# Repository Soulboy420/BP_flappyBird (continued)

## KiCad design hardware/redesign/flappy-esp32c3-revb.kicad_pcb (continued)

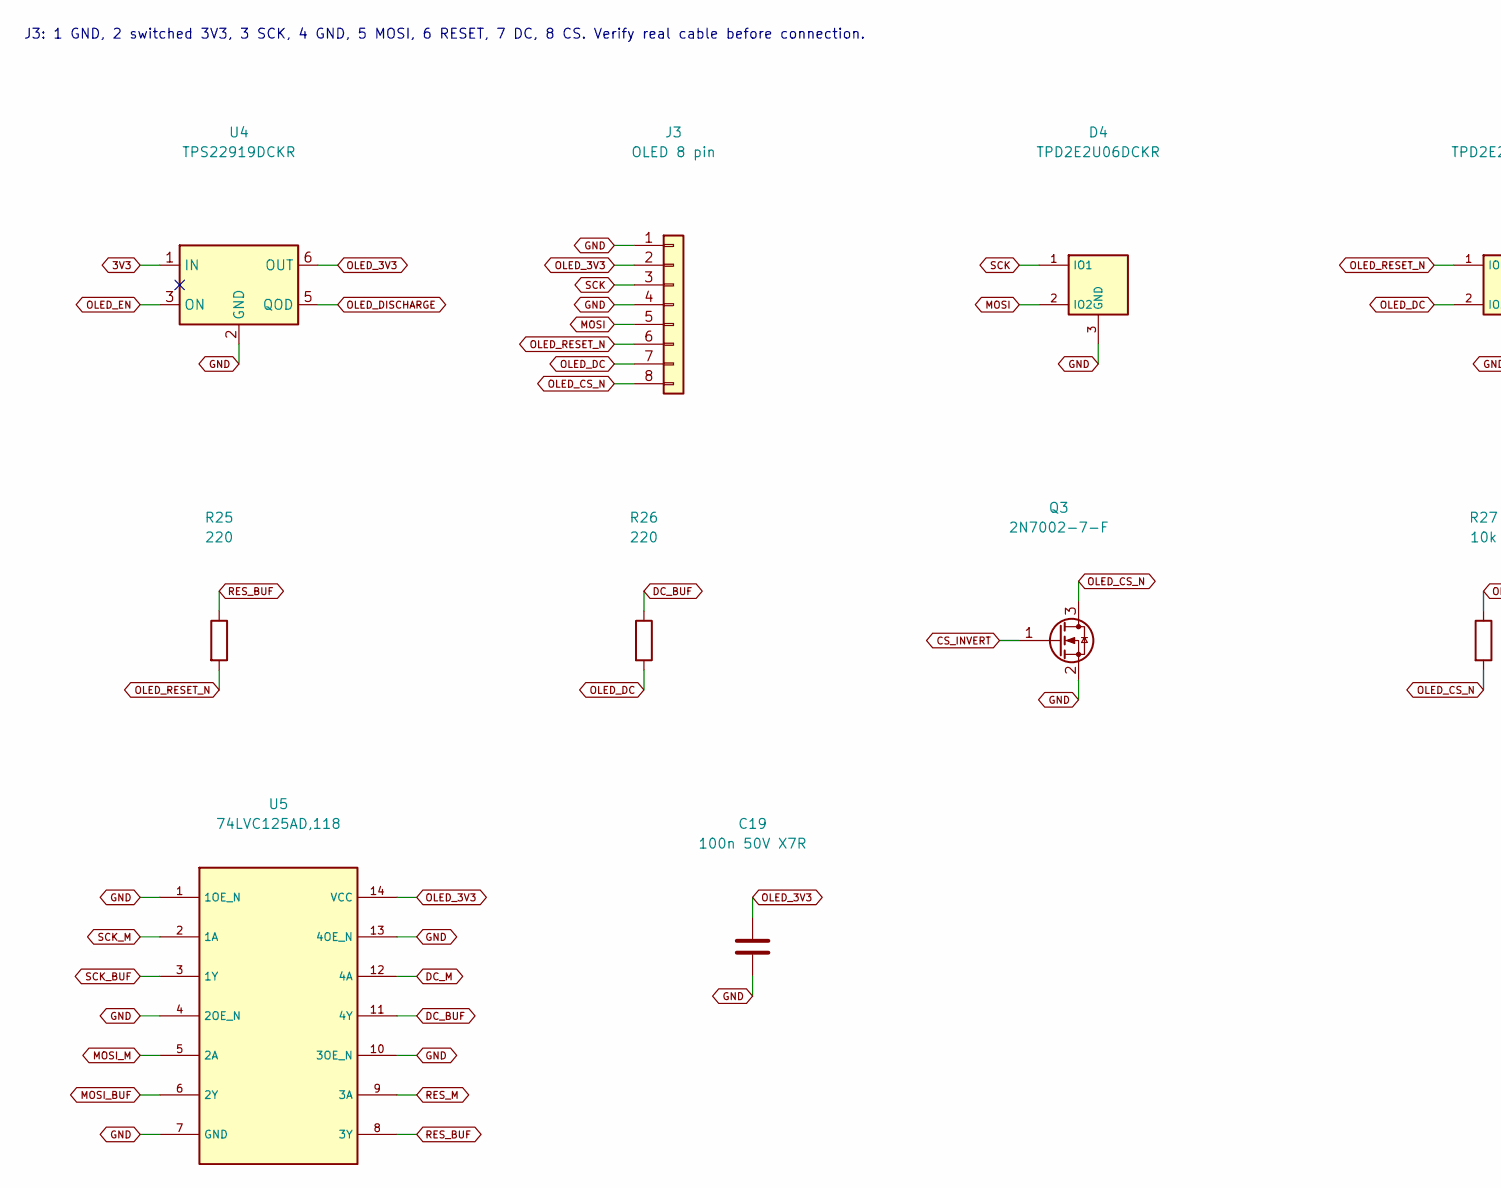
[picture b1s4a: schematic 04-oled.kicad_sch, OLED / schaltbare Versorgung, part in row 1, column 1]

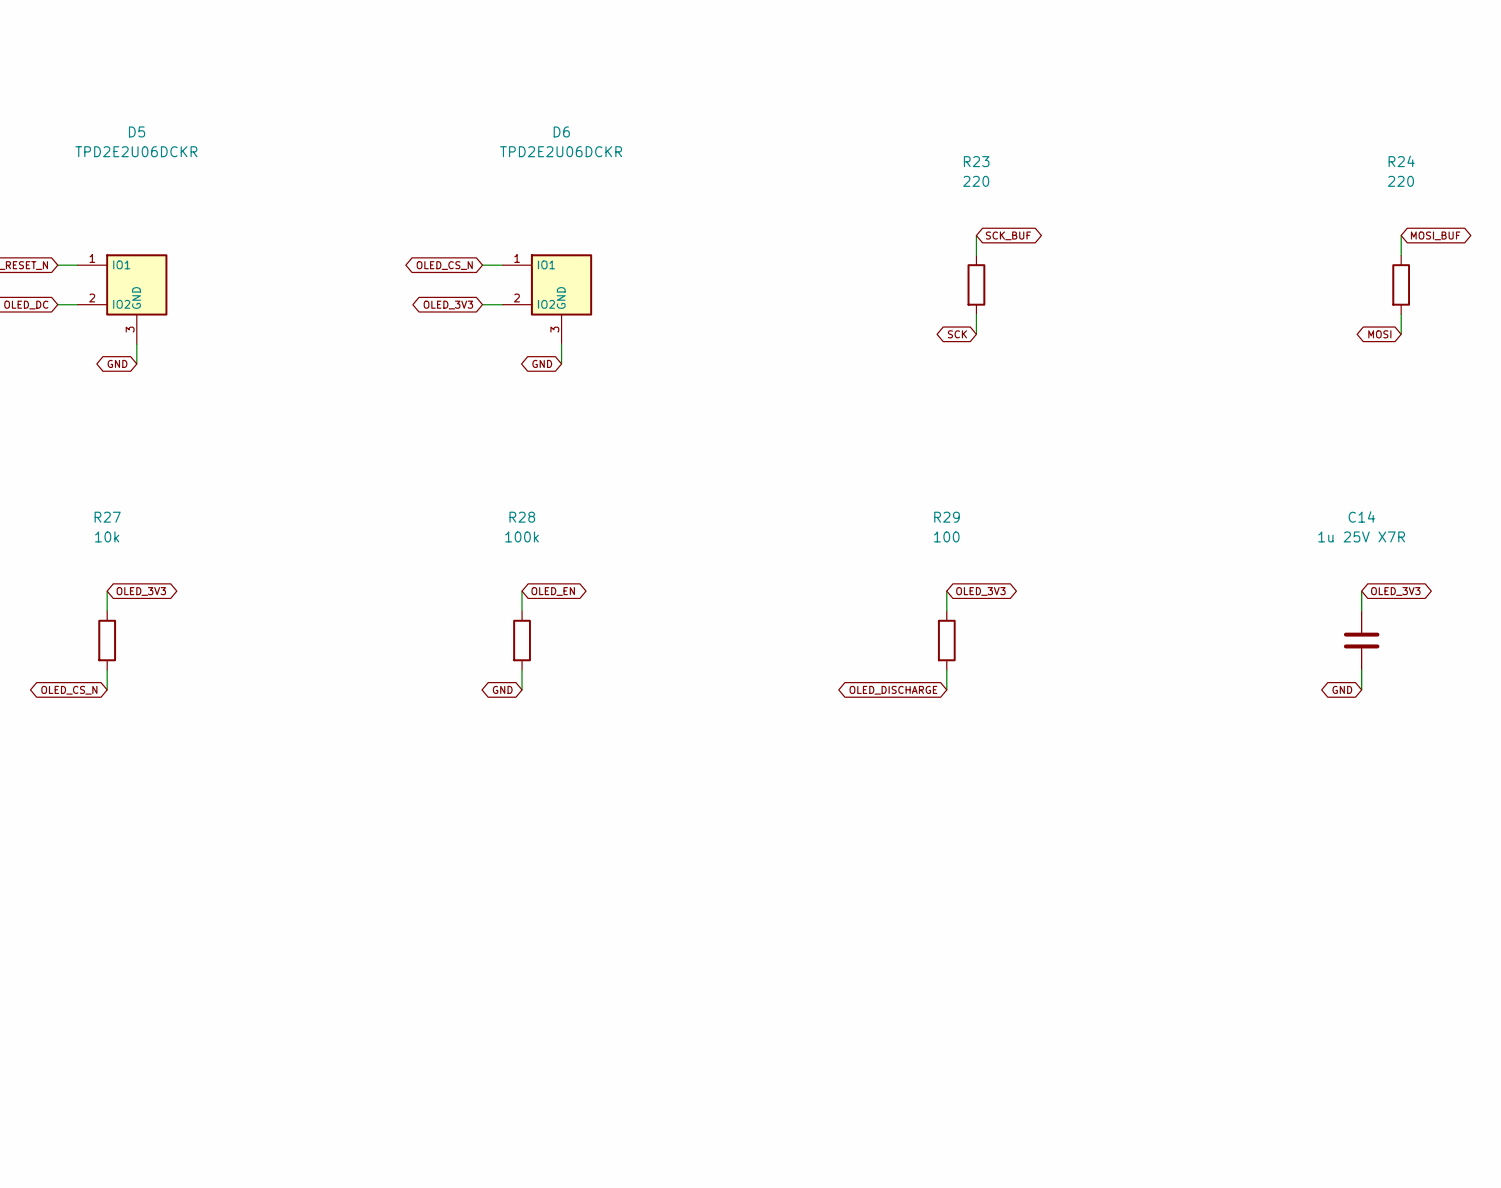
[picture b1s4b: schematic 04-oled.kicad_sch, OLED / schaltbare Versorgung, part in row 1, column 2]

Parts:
C14: 1u 25V X7R; Capacitor_SMD__C_0805_2012Metric_Pad1.18x1.45mm_HandSolder; MPN C2012X7R1E105K125AB
C19: 100n 50V X7R; Capacitor_SMD__C_0805_2012Metric_Pad1.18x1.45mm_HandSolder; MPN C2012X7R1H104K085AA
D4, D5, D6: TPD2E2U06DCKR; Package_TO_SOT_SMD__SOT-323_SC-70; MPN TPD2E2U06DCKR
J3: OLED 8 pin; Connector_JST__JST_XH_B8B-XH-A_1x08_P2.50mm_Vertical; MPN B8B-XH-A(LF)(SN)
Q3: 2N7002-7-F; Package_TO_SOT_SMD__SOT-23; MPN 2N7002-7-F
R23, R24, R25, R26: 220; Resistor_SMD__R_0805_2012Metric_Pad1.20x1.40mm_HandSolder; MPN ERJ-6ENF2200V
R27: 10k; Resistor_SMD__R_0805_2012Metric_Pad1.20x1.40mm_HandSolder; MPN ERJ-6ENF1002V
R28: 100k; Resistor_SMD__R_0805_2012Metric_Pad1.20x1.40mm_HandSolder; MPN ERJ-6ENF1003V
R29: 100; Resistor_SMD__R_0805_2012Metric_Pad1.20x1.40mm_HandSolder; MPN ERJ-6ENF1000V
U4: TPS22919DCKR; Package_TO_SOT_SMD__SOT-363_SC-70-6; MPN TPS22919DCKR
U5: 74LVC125AD,118; Package_SO__SOIC-14_3.9x8.7mm_P1.27mm; MPN 74LVC125AD,118

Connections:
3V3: U4.1 (IN); also elsewhere on the board
CS_INVERT: Q3.1 (G); also elsewhere on the board
DC_BUF: R26.1, U5.11 (4Y)
DC_M: U5.12 (4A); also elsewhere on the board
GND: C14.2, C19.2, D4.3 (GND), D5.3 (GND), D6.3 (GND), J3.1, J3.4, Q3.2 (S), R28.2, U4.2 (GND), U5.1 (1OE_N), U5.4 (2OE_N), U5.7 (GND), U5.10 (3OE_N), U5.13 (4OE_N); also elsewhere on the board
MOSI: D4.2 (IO2), J3.5, R24.2
MOSI_BUF: R24.1, U5.6 (2Y)
MOSI_M: U5.5 (2A); also elsewhere on the board
OLED_3V3: C14.1, C19.1, D6.2 (IO2), J3.2, R27.1, R29.1, U4.6 (OUT), U5.14 (VCC)
OLED_CS_N: D6.1 (IO1), J3.8, Q3.3 (D), R27.2
OLED_DC: D5.2 (IO2), J3.7, R26.2
OLED_DISCHARGE: R29.2, U4.5 (QOD)
OLED_EN: R28.1, U4.3 (ON); also elsewhere on the board
OLED_RESET_N: D5.1 (IO1), J3.6, R25.2
RES_BUF: R25.1, U5.8 (3Y)
RES_M: U5.9 (3A); also elsewhere on the board
SCK: D4.1 (IO1), J3.3, R23.2
SCK_BUF: R23.1, U5.3 (1Y)
SCK_M: U5.2 (1A); also elsewhere on the board

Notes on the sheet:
J3: 1 GND, 2 switched 3V3, 3 SCK, 4 GND, 5 MOSI, 6 RESET, 7 DC, 8 CS. Verify real cable before connection.

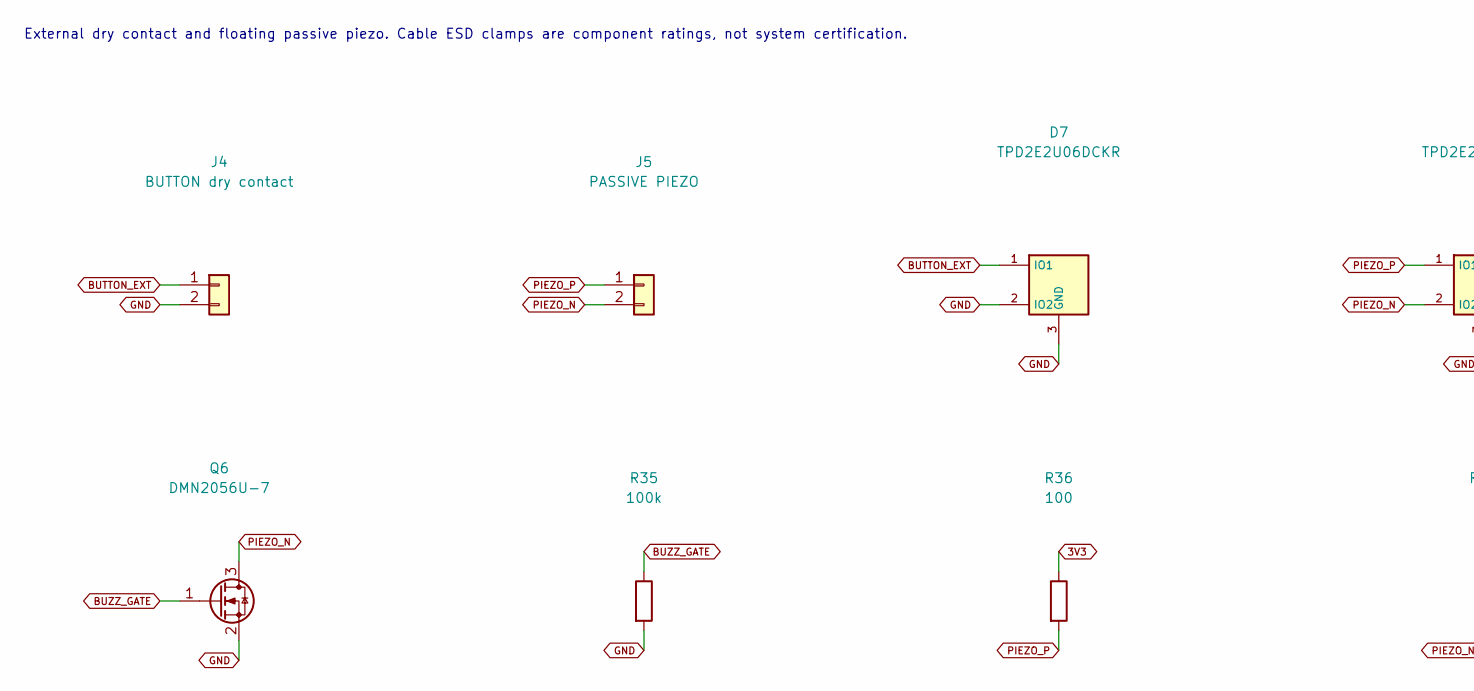
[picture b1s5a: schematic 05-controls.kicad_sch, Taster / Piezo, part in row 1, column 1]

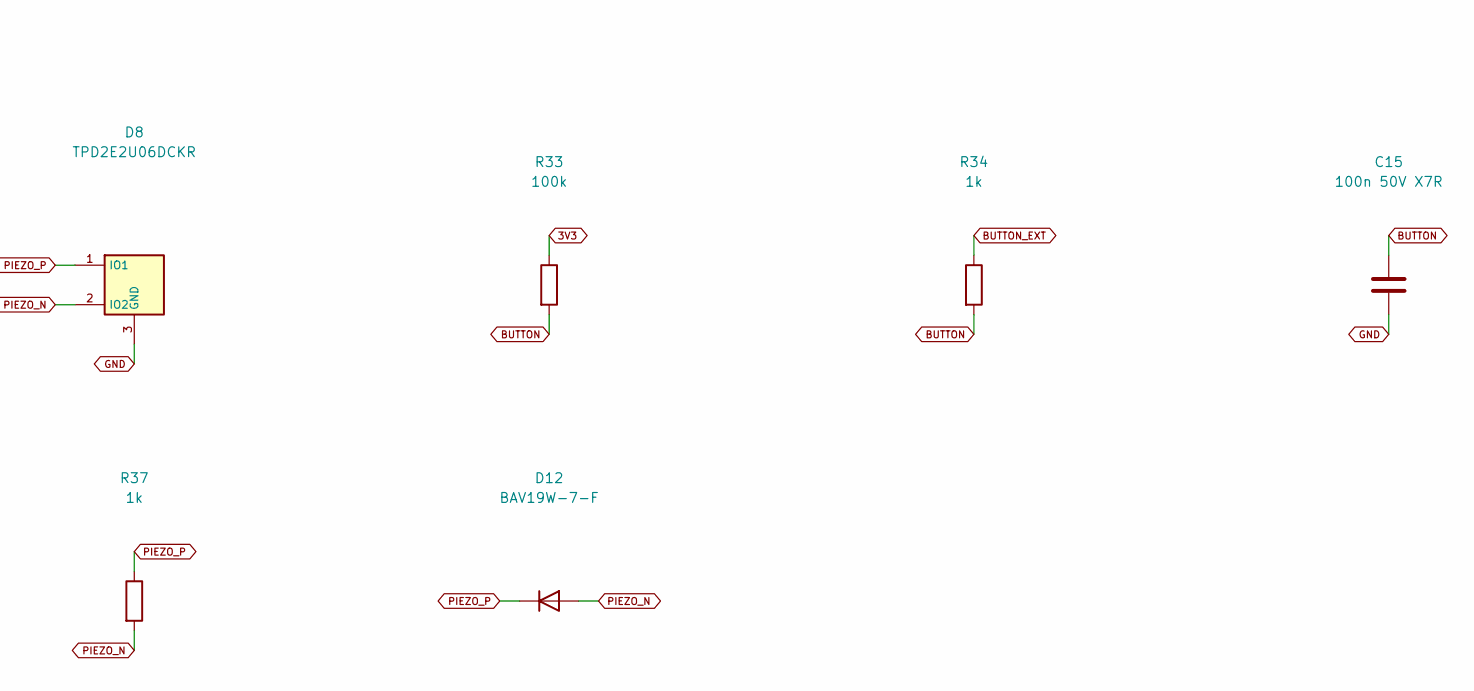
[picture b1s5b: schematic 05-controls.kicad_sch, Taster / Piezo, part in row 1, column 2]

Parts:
C15: 100n 50V X7R; Capacitor_SMD__C_0805_2012Metric_Pad1.18x1.45mm_HandSolder; MPN C2012X7R1H104K085AA
D7, D8: TPD2E2U06DCKR; Package_TO_SOT_SMD__SOT-323_SC-70; MPN TPD2E2U06DCKR
D12: BAV19W-7-F; Diode_SMD__D_SOD-123; MPN BAV19W-7-F
J4: BUTTON dry contact; Connector_JST__JST_XH_B2B-XH-A_1x02_P2.50mm_Vertical; MPN B2B-XH-A(LF)(SN)
J5: PASSIVE PIEZO; Connector_JST__JST_XH_B2B-XH-A_1x02_P2.50mm_Vertical; MPN B2B-XH-A(LF)(SN)
Q6: DMN2056U-7; Package_TO_SOT_SMD__SOT-23; MPN DMN2056U-7
R33, R35: 100k; Resistor_SMD__R_0805_2012Metric_Pad1.20x1.40mm_HandSolder; MPN ERJ-6ENF1003V
R34, R37: 1k; Resistor_SMD__R_0805_2012Metric_Pad1.20x1.40mm_HandSolder; MPN ERJ-6ENF1001V
R36: 100; Resistor_SMD__R_0805_2012Metric_Pad1.20x1.40mm_HandSolder; MPN ERJ-6ENF1000V

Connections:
3V3: R33.1, R36.1; also elsewhere on the board
BUTTON: C15.1, R33.2, R34.2; also elsewhere on the board
BUTTON_EXT: D7.1 (IO1), J4.1, R34.1
BUZZ_GATE: Q6.1 (G), R35.1; also elsewhere on the board
GND: C15.2, D7.2 (IO2), D7.3 (GND), D8.3 (GND), J4.2, Q6.2 (S), R35.2; also elsewhere on the board
PIEZO_N: D8.2 (IO2), D12.2 (A), J5.2, Q6.3 (D), R37.2
PIEZO_P: D8.1 (IO1), D12.1 (K), J5.1, R36.2, R37.1

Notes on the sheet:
External dry contact and floating passive piezo. Cable ESD clamps are component ratings, not system certification.

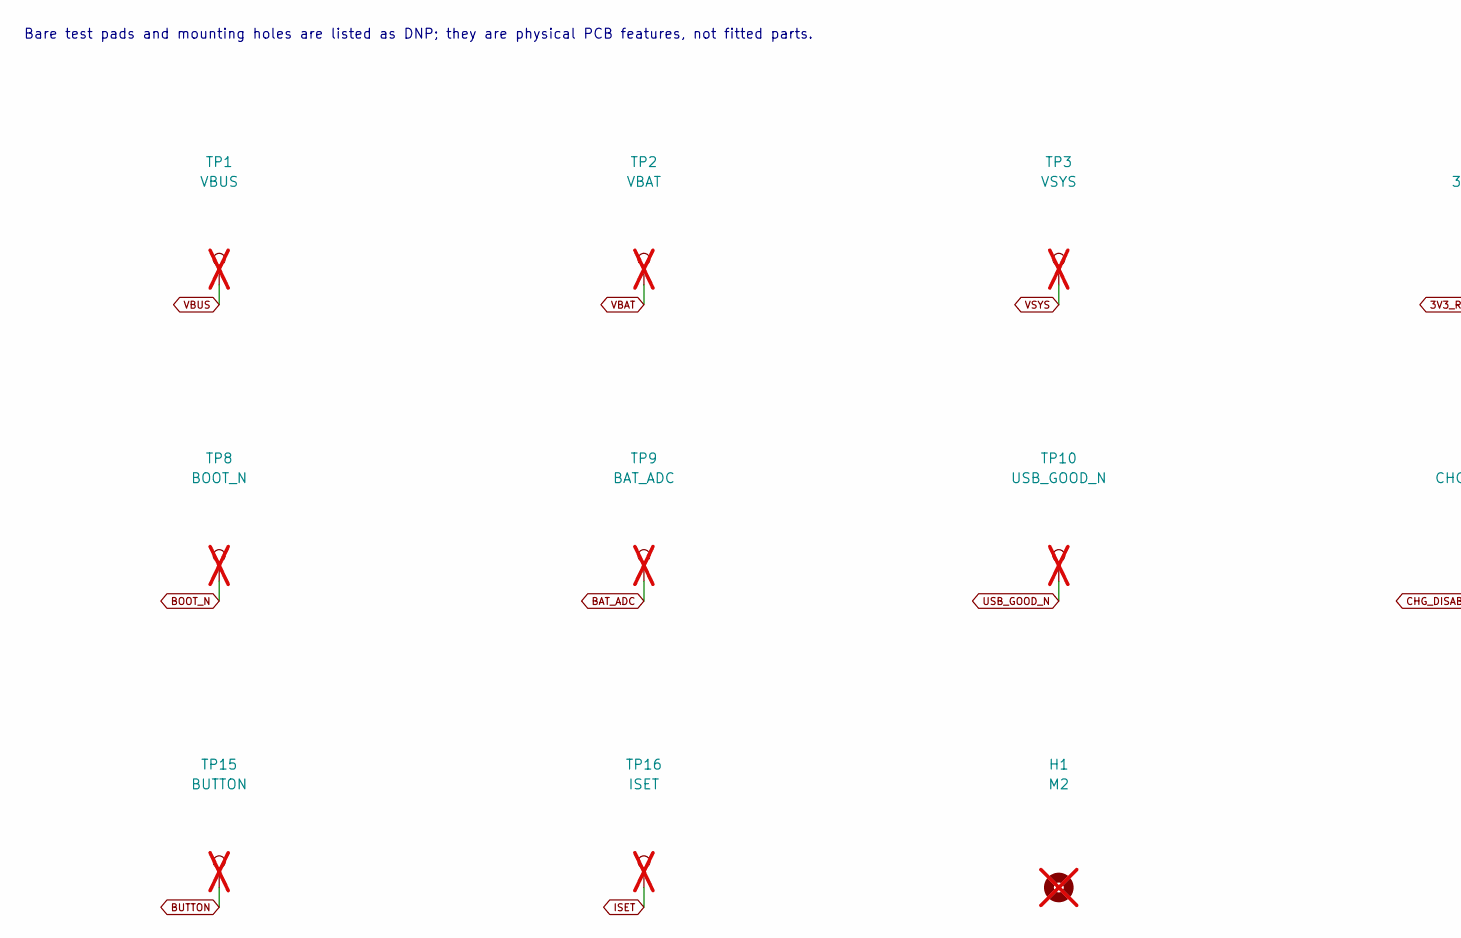
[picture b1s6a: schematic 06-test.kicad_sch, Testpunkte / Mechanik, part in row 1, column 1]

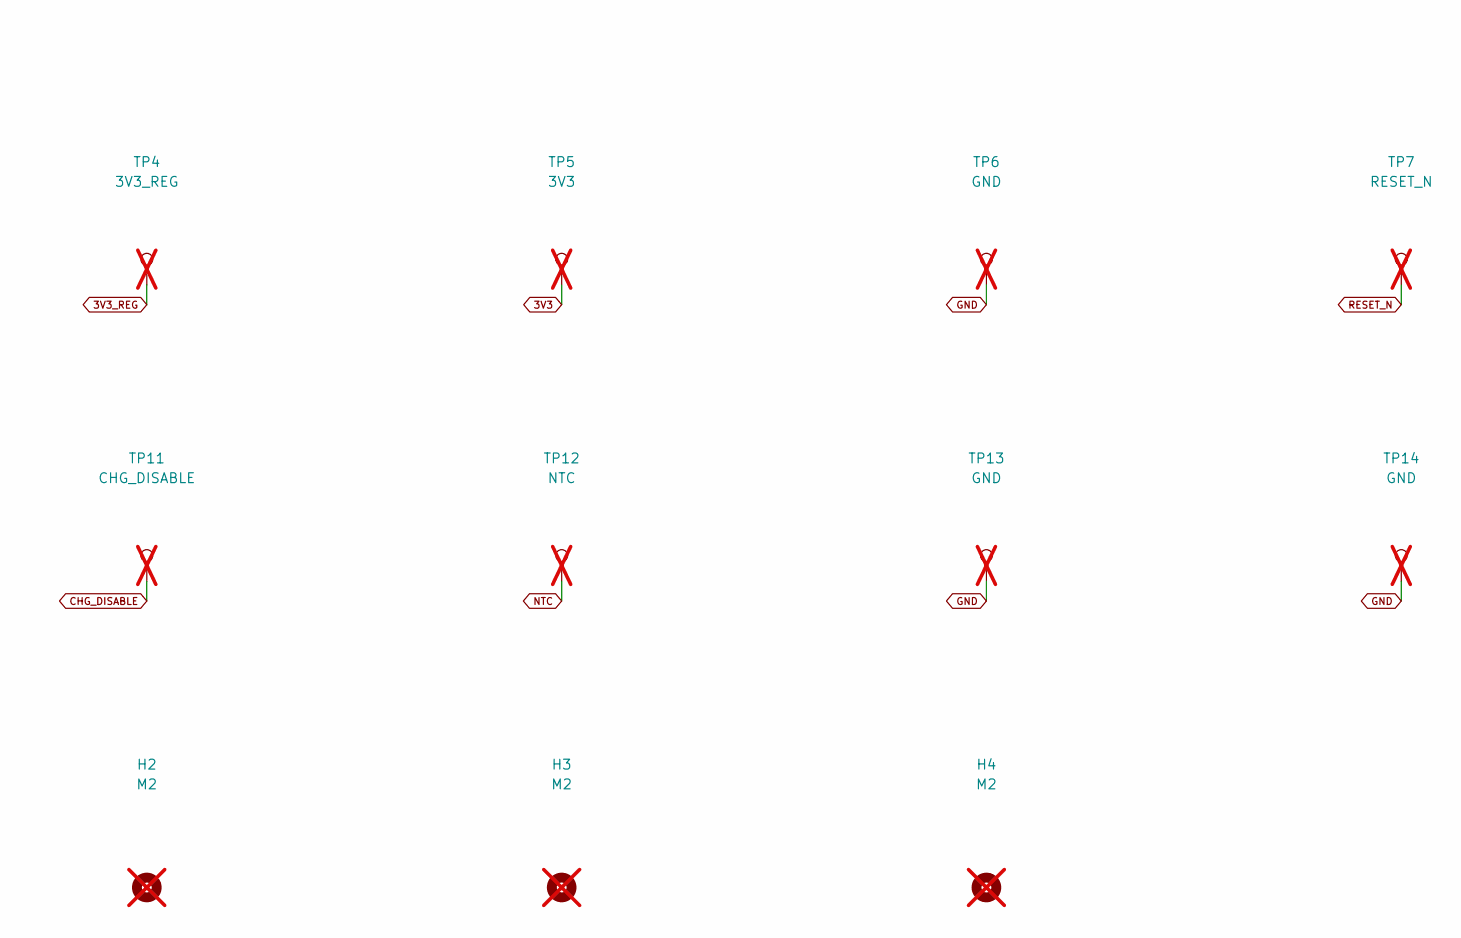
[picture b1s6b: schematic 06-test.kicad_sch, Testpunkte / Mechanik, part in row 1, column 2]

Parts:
H1, H2, H3, H4: M2; MountingHole__MountingHole_2.2mm_M2; MPN N/A - mounting hole; not fitted
TP1: VBUS; TestPoint__TestPoint_Pad_D1.5mm; MPN N/A - bare copper pad; not fitted
TP2: VBAT; TestPoint__TestPoint_Pad_D1.5mm; MPN N/A - bare copper pad; not fitted
TP3: VSYS; TestPoint__TestPoint_Pad_D1.5mm; MPN N/A - bare copper pad; not fitted
TP4: 3V3_REG; TestPoint__TestPoint_Pad_D1.5mm; MPN N/A - bare copper pad; not fitted
TP5: 3V3; TestPoint__TestPoint_Pad_D1.5mm; MPN N/A - bare copper pad; not fitted
TP6, TP13, TP14: GND; TestPoint__TestPoint_Pad_D1.5mm; MPN N/A - bare copper pad; not fitted
TP7: RESET_N; TestPoint__TestPoint_Pad_D1.5mm; MPN N/A - bare copper pad; not fitted
TP8: BOOT_N; TestPoint__TestPoint_Pad_D1.5mm; MPN N/A - bare copper pad; not fitted
TP9: BAT_ADC; TestPoint__TestPoint_Pad_D1.5mm; MPN N/A - bare copper pad; not fitted
TP10: USB_GOOD_N; TestPoint__TestPoint_Pad_D1.5mm; MPN N/A - bare copper pad; not fitted
TP11: CHG_DISABLE; TestPoint__TestPoint_Pad_D1.5mm; MPN N/A - bare copper pad; not fitted
TP12: NTC; TestPoint__TestPoint_Pad_D1.5mm; MPN N/A - bare copper pad; not fitted
TP15: BUTTON; TestPoint__TestPoint_Pad_D1.5mm; MPN N/A - bare copper pad; not fitted
TP16: ISET; TestPoint__TestPoint_Pad_D1.5mm; MPN N/A - bare copper pad; not fitted

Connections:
3V3: TP5.1; also elsewhere on the board
3V3_REG: TP4.1; also elsewhere on the board
BAT_ADC: TP9.1; also elsewhere on the board
BOOT_N: TP8.1; also elsewhere on the board
BUTTON: TP15.1; also elsewhere on the board
CHG_DISABLE: TP11.1; also elsewhere on the board
GND: TP6.1, TP13.1, TP14.1; also elsewhere on the board
ISET: TP16.1; also elsewhere on the board
NTC: TP12.1; also elsewhere on the board
RESET_N: TP7.1; also elsewhere on the board
USB_GOOD_N: TP10.1; also elsewhere on the board
VBAT: TP2.1; also elsewhere on the board
VBUS: TP1.1; also elsewhere on the board
VSYS: TP3.1; also elsewhere on the board

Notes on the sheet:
Bare test pads and mounting holes are listed as DNP; they are physical PCB features, not fitted parts.

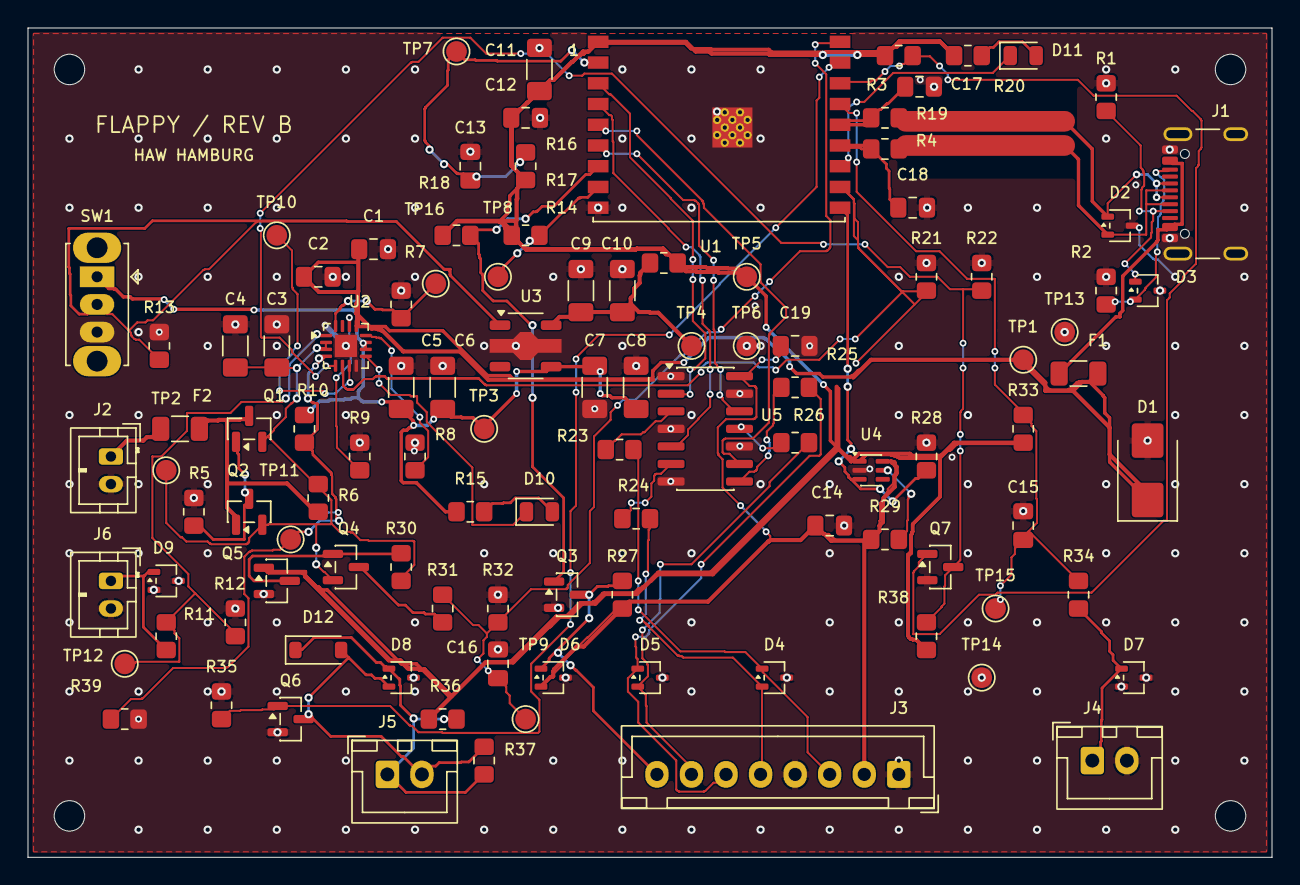
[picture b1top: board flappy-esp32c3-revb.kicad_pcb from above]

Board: 2 copper layers, 90.0 x 60.0 mm, 111 parts (0 on the bottom side), 58 nets.

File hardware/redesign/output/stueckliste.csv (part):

Referenz;Wert;Hersteller;Herstellerteilenummer;Gehaeuse;Footprint;DNP;Anmerkung
U1;ESP32-C3-WROOM-02-N4;Espressif;ESP32-C3-WROOM-02-N4;18x20mm module;RevB:RF_Module__ESP32-C3-WROOM-02;NO;
U2;BQ24074RGTR;Texas Instruments;BQ24074RGTR;VQFN-16 3x3mm EP1.6;RevB:Package_DFN_QFN__VQFN-16-1EP_3x3mm_P0.5mm_EP1.6x1.6mm;NO;"Local reflow mandatory; solder exposed pad; NTC required"
U3;XC6220B331PR-G;Torex;XC6220B331PR-G;SOT-89-5;RevB:Package_TO_SOT_SMD__SOT-89-5;NO;
U4;TPS22919DCKR;Texas Instruments;TPS22919DCKR;SC70-6;RevB:Package_TO_SOT_SMD__SOT-363_SC-70-6;NO;
J1;USB4105-GF-A;GCT;USB4105-GF-A;USB-C 16 SMT + shell THT;RevB:Connector_USB__USB_C_Receptacle_GCT_USB4105-xx-A_16P_TopMnt_Horizontal;NO;
J2;BAT 1S protected;JST;B2B-PH-K-S(LF)(SN);PH 2mm THT;RevB:Connector_JST__JST_PH_B2B-PH-K_1x02_P2.00mm_Vertical;NO;"Pin 1 POSITIVE; independently verify cable, protected 4.2V Li-ion pack only"
J3;OLED 8 pin;JST;B8B-XH-A(LF)(SN);XH 2.5mm THT;RevB:Connector_JST__JST_XH_B8B-XH-A_1x08_P2.50mm_Vertical;NO;"Board pin sequence is fixed; real OLED cable is a release gate"
J4;BUTTON dry contact;JST;B2B-XH-A(LF)(SN);XH 2.5mm THT;RevB:Connector_JST__JST_XH_B2B-XH-A_1x02_P2.50mm_Vertical;NO;
J5;PASSIVE PIEZO;JST;B2B-XH-A(LF)(SN);XH 2.5mm THT;RevB:Connector_JST__JST_XH_B2B-XH-A_1x02_P2.50mm_Vertical;NO;"Floating passive piezo only; no magnetic buzzer; two-wire isolated from chassis"
J6;PACK NTC 10k;JST;B2B-PH-K-S(LF)(SN);PH 2mm THT;RevB:Connector_JST__JST_PH_B2B-PH-K_1x02_P2.00mm_Vertical;NO;"External Semitec 103AT-2 attached to pack; open cable inhibits charging"
SW1;RUN / OFF;C&K (Littelfuse);OS102011MS2QN1;SPDT 2mm THT;RevB:Button_Switch_THT__SW_Slide_SPDT_Straight_CK_OS102011MS2Q;NO;"Only enable current; verify exact switch drawing and cable-free mechanical fit"
R1;5.1k;Panasonic;ERJ-6ENF5101V;0805;RevB:Resistor_SMD__R_0805_2012Metric_Pad1.20x1.40mm_HandSolder;NO;
R2;5.1k;Panasonic;ERJ-6ENF5101V;0805;RevB:Resistor_SMD__R_0805_2012Metric_Pad1.20x1.40mm_HandSolder;NO;
F1;1A fast;Littelfuse;0466001.NRHF;1206;RevB:Fuse__Fuse_1206_3216Metric;NO;
D1;SMBJ6.0A;Littelfuse;SMBJ6.0A;SMB;RevB:Diode_SMD__D_SMB;NO;
C1;1u 25V X7R;TDK;C2012X7R1E105K125AB;0805;RevB:Capacitor_SMD__C_0805_2012Metric_Pad1.18x1.45mm_HandSolder;NO;
C2;100n 50V X7R;TDK;C2012X7R1H104K085AA;0805;RevB:Capacitor_SMD__C_0805_2012Metric_Pad1.18x1.45mm_HandSolder;NO;
D2;TPD2E2U06DCKR;Texas Instruments;TPD2E2U06DCKR;SC70-3;RevB:Package_TO_SOT_SMD__SOT-323_SC-70;NO;
D3;TPD2E2U06DCKR;Texas Instruments;TPD2E2U06DCKR;SC70-3;RevB:Package_TO_SOT_SMD__SOT-323_SC-70;NO;
D4;TPD2E2U06DCKR;Texas Instruments;TPD2E2U06DCKR;SC70-3;RevB:Package_TO_SOT_SMD__SOT-323_SC-70;NO;
D5;TPD2E2U06DCKR;Texas Instruments;TPD2E2U06DCKR;SC70-3;RevB:Package_TO_SOT_SMD__SOT-323_SC-70;NO;
D6;TPD2E2U06DCKR;Texas Instruments;TPD2E2U06DCKR;SC70-3;RevB:Package_TO_SOT_SMD__SOT-323_SC-70;NO;
D7;TPD2E2U06DCKR;Texas Instruments;TPD2E2U06DCKR;SC70-3;RevB:Package_TO_SOT_SMD__SOT-323_SC-70;NO;
D8;TPD2E2U06DCKR;Texas Instruments;TPD2E2U06DCKR;SC70-3;RevB:Package_TO_SOT_SMD__SOT-323_SC-70;NO;
D9;TPD2E2U06DCKR;Texas Instruments;TPD2E2U06DCKR;SC70-3;RevB:Package_TO_SOT_SMD__SOT-323_SC-70;NO;
R3;22;Panasonic;ERJ-6ENF22R0V;0805;RevB:Resistor_SMD__R_0805_2012Metric_Pad1.20x1.40mm_HandSolder;NO;
R4;22;Panasonic;ERJ-6ENF22R0V;0805;RevB:Resistor_SMD__R_0805_2012Metric_Pad1.20x1.40mm_HandSolder;NO;
C17;18p 50V C0G;KEMET (Yageo);C0805C180J5GACTU;0805;RevB:Capacitor_SMD__C_0805_2012Metric_Pad1.18x1.45mm_HandSolder;YES;
C18;18p 50V C0G;KEMET (Yageo);C0805C180J5GACTU;0805;RevB:Capacitor_SMD__C_0805_2012Metric_Pad1.18x1.45mm_HandSolder;YES;
F2;1A fast;Littelfuse;0466001.NRHF;1206;RevB:Fuse__Fuse_1206_3216Metric;NO;
Q1;DMP2035U-7;Diodes Incorporated;DMP2035U-7;SOT-23;RevB:Package_TO_SOT_SMD__SOT-23;NO;
Q2;BSS84-7-F;Diodes Incorporated;BSS84-7-F;SOT-23;RevB:Package_TO_SOT_SMD__SOT-23;NO;
R5;100k;Panasonic;ERJ-6ENF1003V;0805;RevB:Resistor_SMD__R_0805_2012Metric_Pad1.20x1.40mm_HandSolder;NO;
R6;1M;Panasonic;ERJ-6ENF1004V;0805;RevB:Resistor_SMD__R_0805_2012Metric_Pad1.20x1.40mm_HandSolder;YES;"DNP: eliminates DC injection on reverse battery; connect battery before USB, then cycle USB if charge path stays off"
C3;22u 16V X5R;TDK;C3216X5R1C226M160AB;1206;RevB:Capacitor_SMD__C_1206_3216Metric_Pad1.33x1.80mm_HandSolder;NO;"22u: effective capacitance qualification required; no substitution by nominal value only"
C4;22u 16V X5R;TDK;C3216X5R1C226M160AB;1206;RevB:Capacitor_SMD__C_1206_3216Metric_Pad1.33x1.80mm_HandSolder;NO;"22u: effective capacitance qualification required; no substitution by nominal value only"
C5;22u 16V X5R;TDK;C3216X5R1C226M160AB;1206;RevB:Capacitor_SMD__C_1206_3216Metric_Pad1.33x1.80mm_HandSolder;NO;"22u: effective capacitance qualification required; no substitution by nominal value only"
C6;22u 16V X5R;TDK;C3216X5R1C226M160AB;1206;RevB:Capacitor_SMD__C_1206_3216Metric_Pad1.33x1.80mm_HandSolder;NO;"22u: effective capacitance qualification required; no substitution by nominal value only"
C7;22u 16V X5R;TDK;C3216X5R1C226M160AB;1206;RevB:Capacitor_SMD__C_1206_3216Metric_Pad1.33x1.80mm_HandSolder;NO;"22u: effective capacitance qualification required; no substitution by nominal value only"
C8;22u 16V X5R;TDK;C3216X5R1C226M160AB;1206;RevB:Capacitor_SMD__C_1206_3216Metric_Pad1.33x1.80mm_HandSolder;NO;"22u: effective capacitance qualification required; no substitution by nominal value only"
C9;22u 16V X5R;TDK;C3216X5R1C226M160AB;1206;RevB:Capacitor_SMD__C_1206_3216Metric_Pad1.33x1.80mm_HandSolder;NO;"22u: effective capacitance qualification required; no substitution by nominal value only"
C10;22u 16V X5R;TDK;C3216X5R1C226M160AB;1206;RevB:Capacitor_SMD__C_1206_3216Metric_Pad1.33x1.80mm_HandSolder;NO;"22u: effective capacitance qualification required; no substitution by nominal value only"
R7;6.19k;Panasonic;ERJ-6ENF6191V;0805;RevB:Resistor_SMD__R_0805_2012Metric_Pad1.20x1.40mm_HandSolder;NO;"143.8mA nominal; 127.5..159.1mA with 1% resistor and KISET limits"
R8;3.24k;Panasonic;ERJ-6ENF3241V;0805;RevB:Resistor_SMD__R_0805_2012Metric_Pad1.20x1.40mm_HandSolder;NO;"Required even in USB mode; programmable mode unused"
R9;46.4k;Panasonic;ERJ-6ENF4642V;0805;RevB:Resistor_SMD__R_0805_2012Metric_Pad1.20x1.40mm_HandSolder;NO;6.19h nominal fast-charge safety timer
R10;100k;Panasonic;ERJ-6ENF1003V;0805;RevB:Resistor_SMD__R_0805_2012Metric_Pad1.20x1.40mm_HandSolder;NO;Default charging DISABLED. Populate R39 only after battery/temperature release
R11;100;Panasonic;ERJ-6ENF1000V;0805;RevB:Resistor_SMD__R_0805_2012Metric_Pad1.20x1.40mm_HandSolder;NO;
R12;10k;Panasonic;ERJ-6ENF1002V;0805;RevB:Resistor_SMD__R_0805_2012Metric_Pad1.20x1.40mm_HandSolder;YES;BENCH ONLY / NO BATTERY: defeats pack temperature sensing
R13;1M;Panasonic;ERJ-6ENF1004V;0805;RevB:Resistor_SMD__R_0805_2012Metric_Pad1.20x1.40mm_HandSolder;NO;
R14;0;Panasonic;ERJ-6GEY0R00V;0805;RevB:Resistor_SMD__R_0805_2012Metric_Pad1.20x1.40mm_HandSolder;NO;"Remove for total switched-system current measurement; pads accessible"
R15;3.3k;Panasonic;ERJ-6ENF3301V;0805;RevB:Resistor_SMD__R_0805_2012Metric_Pad1.20x1.40mm_HandSolder;NO;
D10;CHARGE red;Kingbright;APT2012EC;0805;RevB:LED_SMD__LED_0805_2012Metric;NO;
C11;22u 16V X5R;TDK;C3216X5R1C226M160AB;1206;RevB:Capacitor_SMD__C_1206_3216Metric_Pad1.33x1.80mm_HandSolder;NO;"22u: effective capacitance qualification required; no substitution by nominal value only"
C12;100n 50V X7R;TDK;C2012X7R1H104K085AA;0805;RevB:Capacitor_SMD__C_0805_2012Metric_Pad1.18x1.45mm_HandSolder;NO;
R16;10k;Panasonic;ERJ-6ENF1002V;0805;RevB:Resistor_SMD__R_0805_2012Metric_Pad1.20x1.40mm_HandSolder;NO;
C13;1u 25V X7R;TDK;C2012X7R1E105K125AB;0805;RevB:Capacitor_SMD__C_0805_2012Metric_Pad1.18x1.45mm_HandSolder;NO;
R17;10k;Panasonic;ERJ-6ENF1002V;0805;RevB:Resistor_SMD__R_0805_2012Metric_Pad1.20x1.40mm_HandSolder;NO;
R18;10k;Panasonic;ERJ-6ENF1002V;0805;RevB:Resistor_SMD__R_0805_2012Metric_Pad1.20x1.40mm_HandSolder;NO;
R19;10k;Panasonic;ERJ-6ENF1002V;0805;RevB:Resistor_SMD__R_0805_2012Metric_Pad1.20x1.40mm_HandSolder;NO;
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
